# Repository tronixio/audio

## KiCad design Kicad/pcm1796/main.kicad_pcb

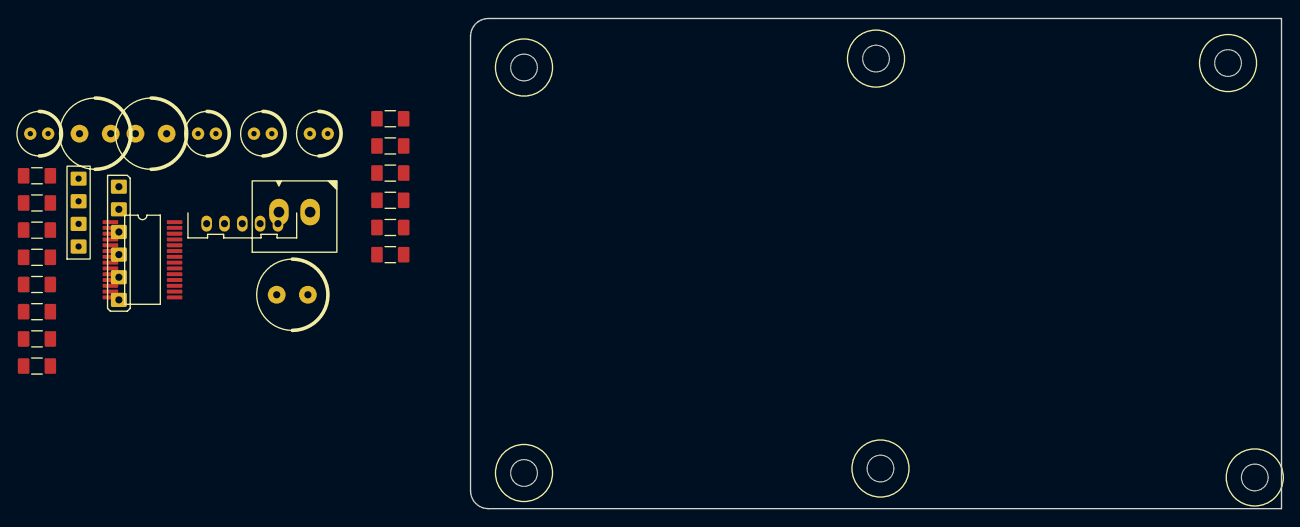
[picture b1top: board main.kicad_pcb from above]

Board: 2 copper layers, 91.0 x 55.0 mm, 34 parts (0 on the bottom side), 13 nets, no tracks yet.

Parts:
C101, C203, C204: 47µ; CAPACITOR-ELECTROLYTIC-RADIAL-080-115-035-WURTH
C102, C103, C104, C105, C106, C107: 1µ; CAPACITOR-SMD-1206
C201, C205, C207, C209: 10µ; CAPACITOR-ELECTROLYTIC-RADIAL-050-110-020-WURTH
C202, C206, C208: 100n; CAPACITOR-SMD-1206
H101, H102, H103, H104, H105, H106: MOUNTING-HOLE-3MM-MASK
K101: VCC; MOLEX-532580229
K201: I2S; MOLEX-532530570
K202: MCU; HARWIN-M20-999064x
K203: CLOCK; HARWIN-M20-782044x
R201, R202, R203: 27Ω; RESISTOR-SMD-1206
R204: 10Ω; RESISTOR-SMD-1206
R205: 10K; RESISTOR-SMD-1206
U201: PCM1795/6; SSOP-28
kibuzzard-63CAF235: G***; kibuzzard-63CAF235
kibuzzard-63CBA350: G***; kibuzzard-63CBA350

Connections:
+3V3: C103.1, C201.1, C202.1, K203.1, U201.3 (MSEL), U201.9 (VDD)
+5V: C105.1, C203.1, C204.1, C205.1, U201.23 (VCC1)
+5VA: C107.1, C206.1, C207.1, C208.1, C209.1, U201.15 (VCC2R), U201.28 (VCC2L)
AGND: C101.2, C102.2, C103.2, C104.2, C105.2, C106.2, C107.2, C201.2, C202.2, C205.2, C206.2, C207.2, C208.2, C209.2, K101.1, K201.5, K202.6, K203.4, R205.2, U201.8 (DGND), U201.10 (ADR0/~MS), U201.11 (ADR1/MDI), U201.16 (AGND3R), U201.19 (AGND1), U201.24 (AGND2), U201.27 (AGND3L)
unnamed: R205.1, U201.20 (IREF)
unnamed: K202.2, U201.12 (SCL/MC)
unnamed: K202.3, U201.13 (SDA/MDO)
unnamed: C204.2, U201.22 (VCOML)
unnamed: C203.2, U201.21 (VCOMR)
unnamed: K202.4, U201.1 (ZEROL)
unnamed: K202.5, U201.2 (ZEROR)
unnamed: K202.1, U201.14 (~RST)
VCC: C101.1, C102.1, C104.1, C106.1, K101.2
